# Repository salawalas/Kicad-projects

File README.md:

This is a base of my KiCad projects.

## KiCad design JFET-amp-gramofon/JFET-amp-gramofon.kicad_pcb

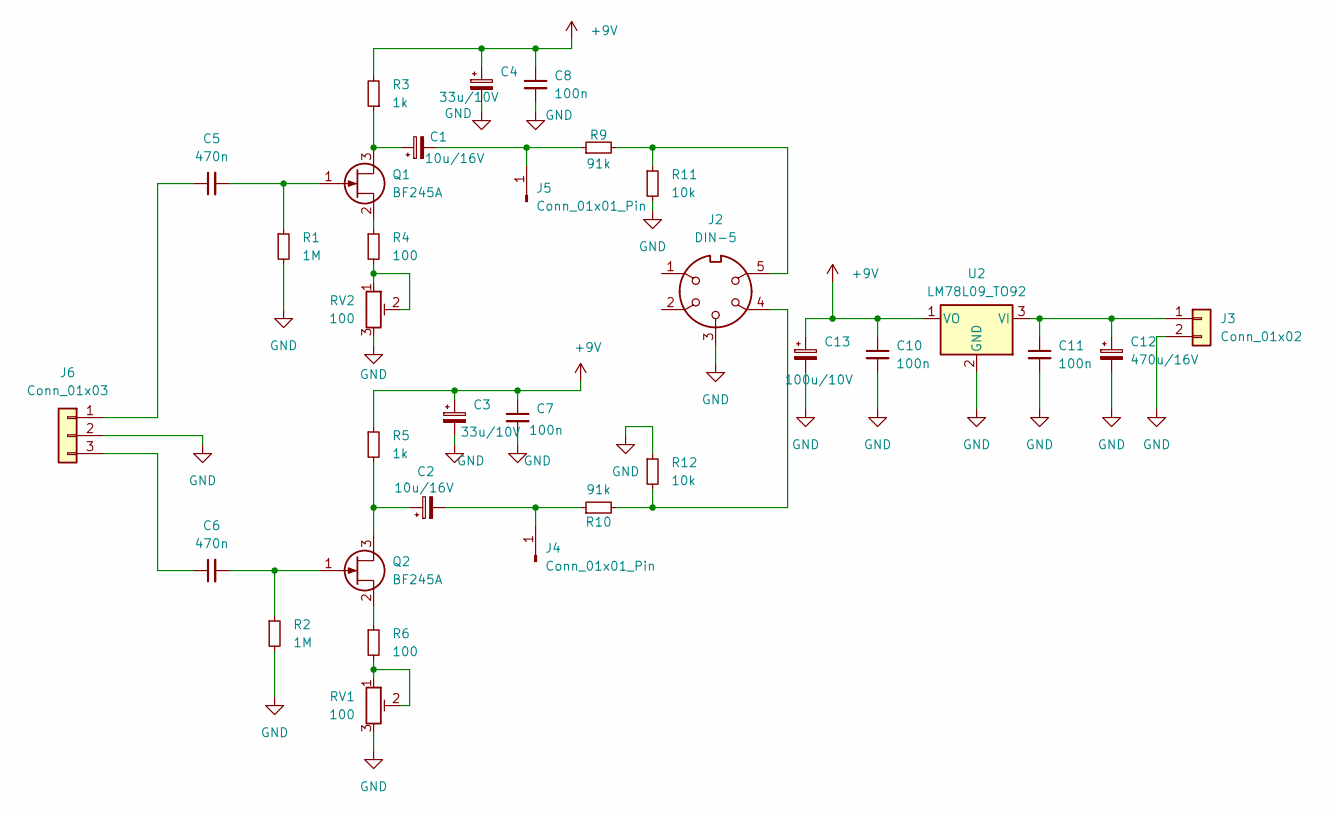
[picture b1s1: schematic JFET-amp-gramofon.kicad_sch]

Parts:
C1, C2: 10u/16V; CP_Radial_D6.3mm_P2.50mm
C3, C4: 33u/10V; CP_Radial_Tantal_D5.5mm_P5.00mm
C5, C6: 470n; C_0805_2012Metric
C7, C8, C10, C11: 100n; C_1206_3216Metric_Pad1.33x1.80mm_HandSolder
C12: 470u/16V; CP_Radial_D10.0mm_P5.00mm
C13: 100u/10V; CP_Radial_D8.0mm_P2.50mm
J2: DIN-5; DIN_5
J3: Conn_01x02; Molex_KK-254_AE-6410-02A_1x02_P2.54mm_Vertical
J4, J5: Conn_01x01_Pin; Pin_D1.3mm_L11.0mm
J6: Conn_01x03; JST_PH_B3B-PH-K_1x03_P2.00mm_Vertical
Q1, Q2: BF245A; TO-92_HandSolder
R1, R2: 1M; R_1206_3216Metric_Pad1.30x1.75mm_HandSolder
R3, R5: 1k; R_1206_3216Metric_Pad1.30x1.75mm_HandSolder
R4, R6: 100; R_1206_3216Metric_Pad1.30x1.75mm_HandSolder
R9, R10: 91k; R_1206_3216Metric_Pad1.30x1.75mm_HandSolder
R11, R12: 10k; R_1206_3216Metric_Pad1.30x1.75mm_HandSolder
RV1, RV2: 100; Potencjometr-smd-mały
U2: LM78L09_TO92; TO-92L_HandSolder

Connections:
+9V: C3.1, C4.1, C7.1, C8.1, C10.1, C13.1, R3.2, R5.1, U2.1 (VO)
GND: C3.2, C4.2, C7.2, C8.2, C10.2, C11.2, C12.2, C13.2, J2.3, J3.2, J6.2, R1.2, R2.2, R11.2, R12.1, RV1.3, RV2.3, U2.2 (GND)
unnamed: J2.4, R10.2, R12.2
unnamed: J2.5, R9.2, R11.1
unnamed: C11.1, C12.1, J3.1, U2.3 (VI)
unnamed: C2.2, J4.1, R10.1
unnamed: C1.2, J5.1, R9.1
unnamed: C5.1, J6.1
unnamed: C6.1, J6.3
unnamed: C1.1, Q1.3 (D), R3.1
unnamed: C5.2, Q1.1 (G), R1.1
unnamed: Q1.2 (S), R4.1
unnamed: C2.1, Q2.3 (D), R5.2
unnamed: C6.2, Q2.1 (G), R2.1
unnamed: Q2.2 (S), R6.1
unnamed: R4.2, RV2.1, RV2.2
unnamed: R6.2, RV1.1, RV1.2

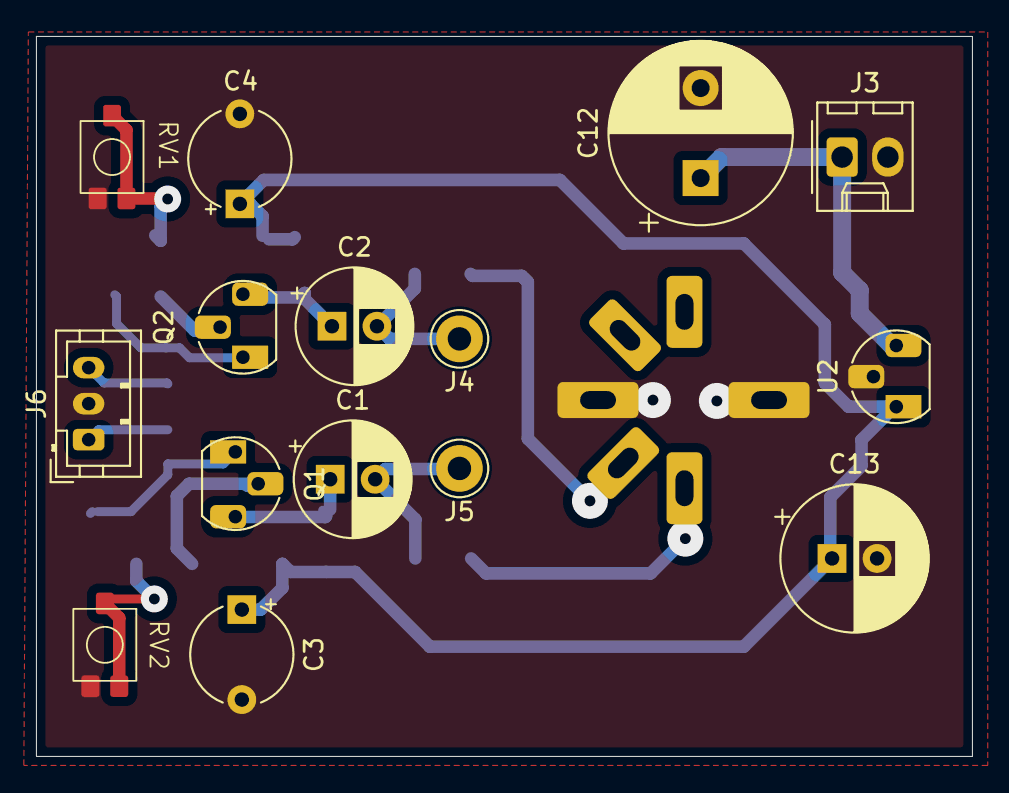
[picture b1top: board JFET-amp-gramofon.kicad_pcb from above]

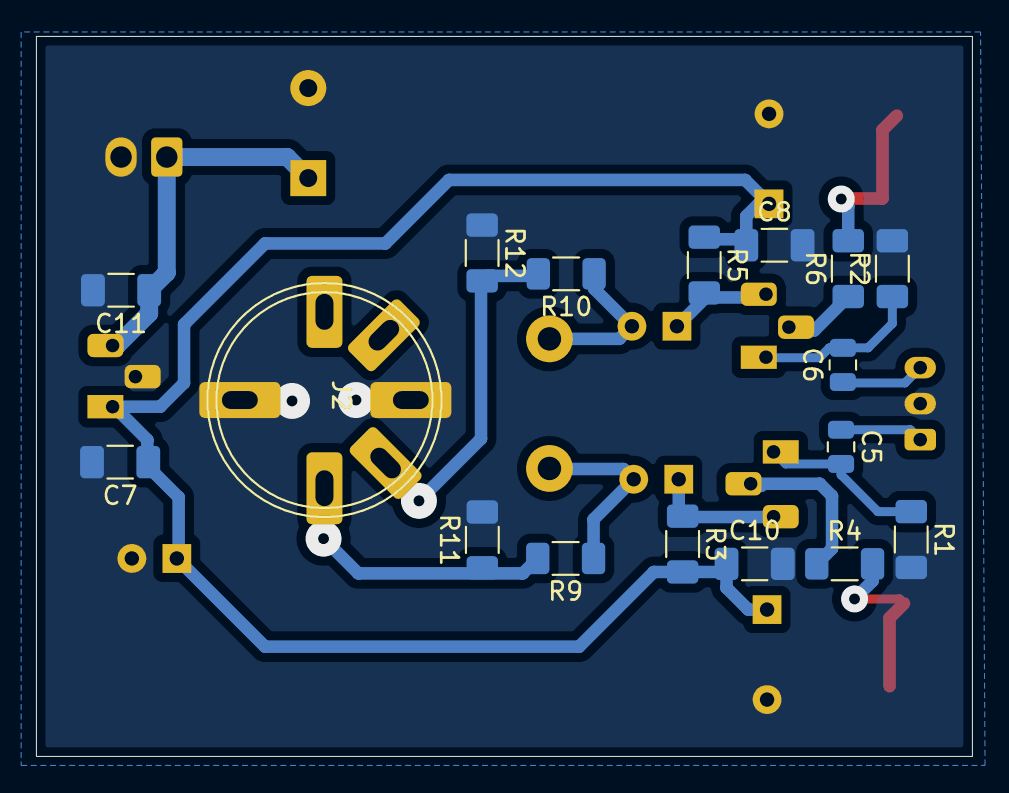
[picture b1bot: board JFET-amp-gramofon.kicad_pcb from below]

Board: 2 copper layers, 52.0 x 40.0 mm, 32 parts (17 on the bottom side), 17 nets.

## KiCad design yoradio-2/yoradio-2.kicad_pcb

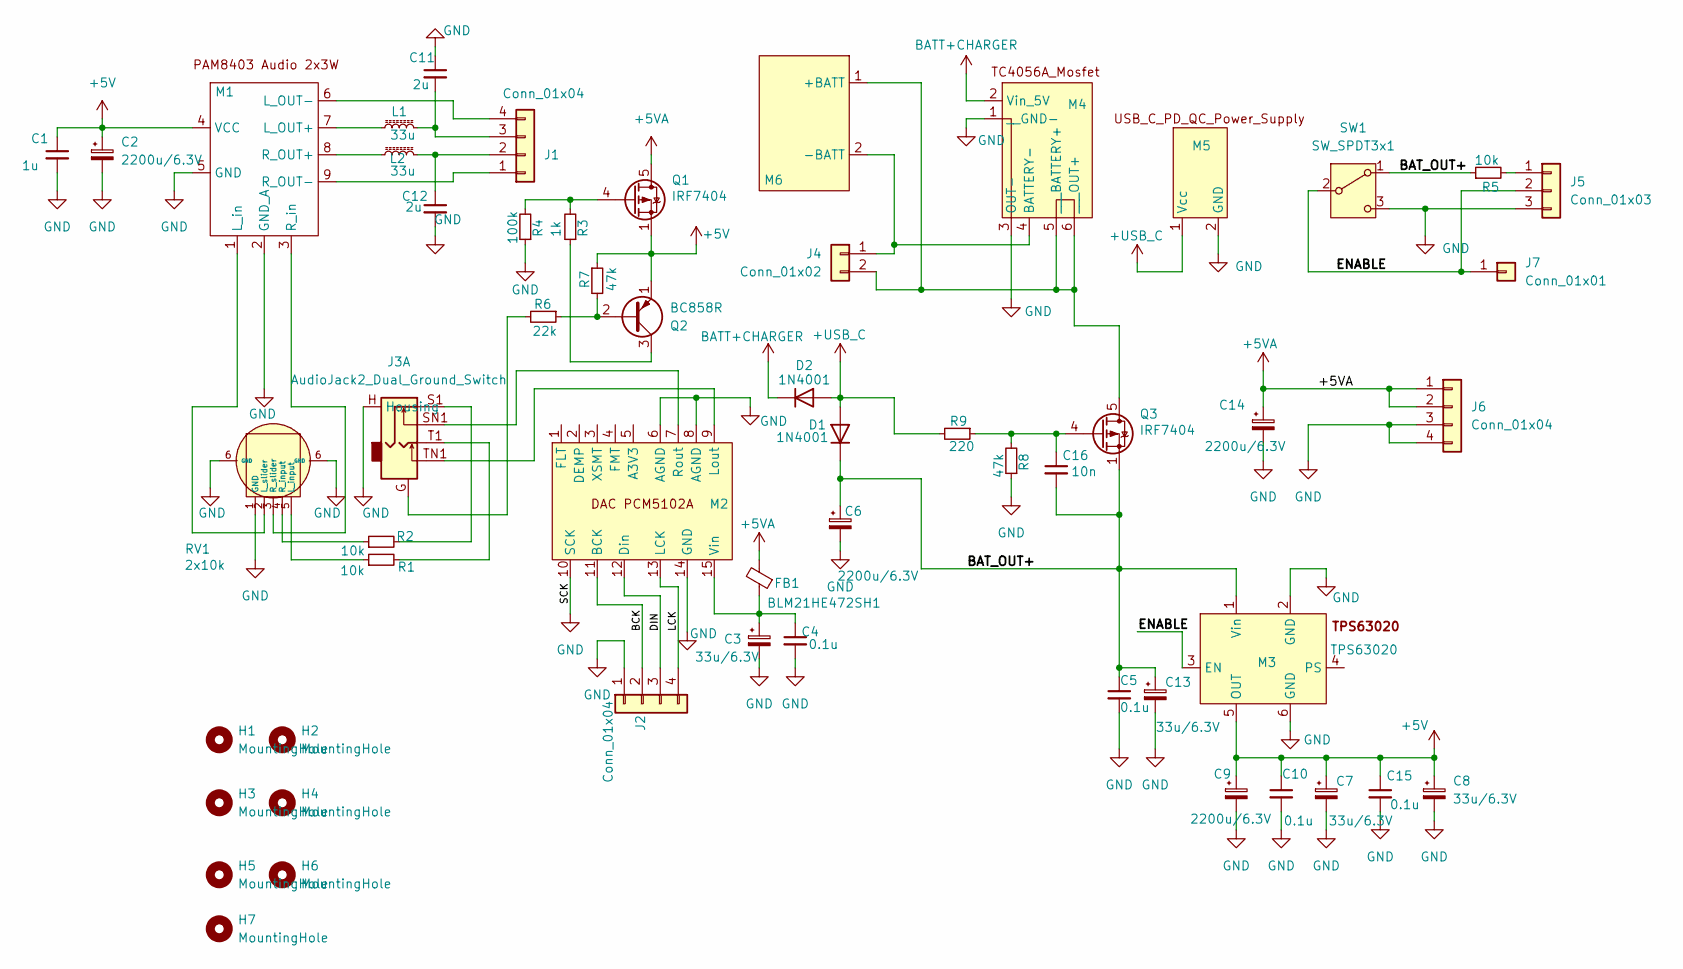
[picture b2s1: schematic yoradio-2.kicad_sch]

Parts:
C1: 1u; C_1206_3216Metric_Pad1.33x1.80mm_HandSolder
C2, C6, C9, C14: 2200u/6.3V; 2200u_6.3V
C3, C7, C8, C13: 33u/6.3V; CP_Radial_Tantal_D5.0mm_P2.50mm
C4, C5, C10, C15: 0.1u; C_1206_3216Metric_Pad1.33x1.80mm_HandSolder
C11, C12: 2u; C_1206_3216Metric_Pad1.33x1.80mm_HandSolder
C16: 10n; C_1206_3216Metric_Pad1.33x1.80mm_HandSolder
D1, D2: 1N4001; D_DO-41_SOD81_P10.16mm_Horizontal
FB1: BLM21HE472SH1; L_0805_2012Metric
H1, H2, H3, H4, H5, H6, H7: MountingHole; MountingHole_2.5mm
J1: Conn_01x04; JST_XH_B4B-XH-A_1x04_P2.50mm_Vertical
J2: Conn_01x04; JST_PH_B4B-PH-K_1x04_P2.00mm_Vertical
J3: AudioJack2_Dual_Ground_Switch; Jack_3.5mm_PJ31060-I_Horizontal
J4: Conn_01x02; Molex_KK-254_AE-6410-02A_1x02_P2.54mm_Vertical
J5: Conn_01x03; JST_PH_B3B-PH-K_1x03_P2.00mm_Vertical
J6: Conn_01x04; Molex_KK-254_AE-6410-04A_1x04_P2.54mm_Vertical
J7: Conn_01x01; SolderWire-0.5sqmm_1x01_D0.9mm_OD2.1mm
L1, L2: 33u; L_Radial_D7.0mm_P3.00mm
M1: PAM8403_Audio_2x3W_
M2: DAC_PCM5102DAC_PCM5102
M3: TPS63020; TPS63020_module
M4: TC4056A_Mosfet
M5: USB_C_PD_QC_Power_SupplyUSB_C_PS
M6: Wskaznik_LED_1S_Lipo
Q1, Q3: IRF7404; SOIC-8_3.9x4.9mm_P1.27mm
Q2: BC858R; SOT-23
R1, R2, R5: 10k; R_0805_2012Metric_Pad1.20x1.40mm_HandSolder
R3: 1k; R_1206_3216Metric
R4: 100k; R_1206_3216Metric
R6: 22k; R_1206_3216Metric
R7: 47k; R_0805_2012Metric
R8: 47k; R_1206_3216Metric
R9: 220; R_1206_3216Metric
RV1: 2x10k; Potencjometr_podwójny_thumbwheel.mp3
SW1: SW_SPDT3x1

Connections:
+5V: C1.1, C2.1, C7.1, C8.1, C9.1, C10.1, C15.1, M1.4 (VCC), M3.5 (OUT), Q1.1 (S), Q1.2 (S), Q1.3 (S), Q2.1 (E), R7.1
+5VA: C14.1, FB1.2, J6.1, J6.2, Q1.5 (D), Q1.6 (D), Q1.7 (D), Q1.8 (D)
+USB_C: D1.2 (A), D2.2 (A), M5.1 (Vcc), R9.2
/BAT_OUT+: C5.1, C6.1, C13.1, C16.2, D1.1 (K), M3.1 (Vin), Q3.1 (S), Q3.2 (S), Q3.3 (S), R5.1, SW1.1 (A)
/BCK: J2.2, M2.11 (BCK)
/DIN: J2.3, M2.12 (Din)
/ENABLE: J5.2, J7.1, M3.3 (EN), SW1.2 (B)
/LCK: J2.4, M2.13 (LCK)
BATT+CHARGER: D2.1 (K), M4.2 (Vin_5V)
GND: C1.2, C2.2, C3.2, C4.2, C5.2, C6.2, C7.2, C8.2, C9.2, C10.2, C11.1, C12.2, C13.2, C14.2, C15.2, J2.1, J3.H (Housing), J5.3, J6.3, J6.4, M1.2 (GND_A), M1.5 (GND), M2.6 (AGND), M2.8 (AGND), M2.10 (SCK), M2.14 (GND), M3.2 (GND), M3.6 (GND), M4.1 (__GND-), M4.3 (OUT-), M5.2 (GND), R4.1, R8.1, RV1.1 (GND), RV1.6 (GND), SW1.3 (C)
unnamed: J1.1, M1.9 (R_OUT-)
unnamed: C12.1, J1.2, L2.2
unnamed: C11.2, J1.3, L1.2
unnamed: J1.4, M1.6 (L_OUT-)
unnamed: J3.G, R6.2
unnamed: J3.S1, R2.2
unnamed: J3.T1, R1.2
unnamed: J4.1, M4.4 (BATTERY-), M6.2 (-BATT)
unnamed: J4.2, M4.5 (___BATTERY+), M4.6 (___OUT+), M6.1 (+BATT), Q3.5 (D), Q3.6 (D), Q3.7 (D), Q3.8 (D)
unnamed: J5.1, R5.2
unnamed: L1.1, M1.7 (L_OUT+)
unnamed: M1.1 (L_in), RV1.2 (L_slider)
unnamed: L2.1, M1.8 (R_OUT+)
unnamed: M1.3 (R_in), RV1.3 (R_slider)
unnamed: J3.TN1, M2.9 (Lout)
unnamed: J3.SN1, M2.7 (Rout)
unnamed: C3.1, C4.1, FB1.1, M2.15 (Vin)
unnamed: Q1.4 (G), R3.2, R4.2
unnamed: Q2.2 (B), R6.1, R7.2
unnamed: Q2.3 (C), R3.1
unnamed: C16.1, Q3.4 (G), R8.2, R9.1
unnamed: R1.1, RV1.5 (L_input)
unnamed: R2.1, RV1.4 (R_input)

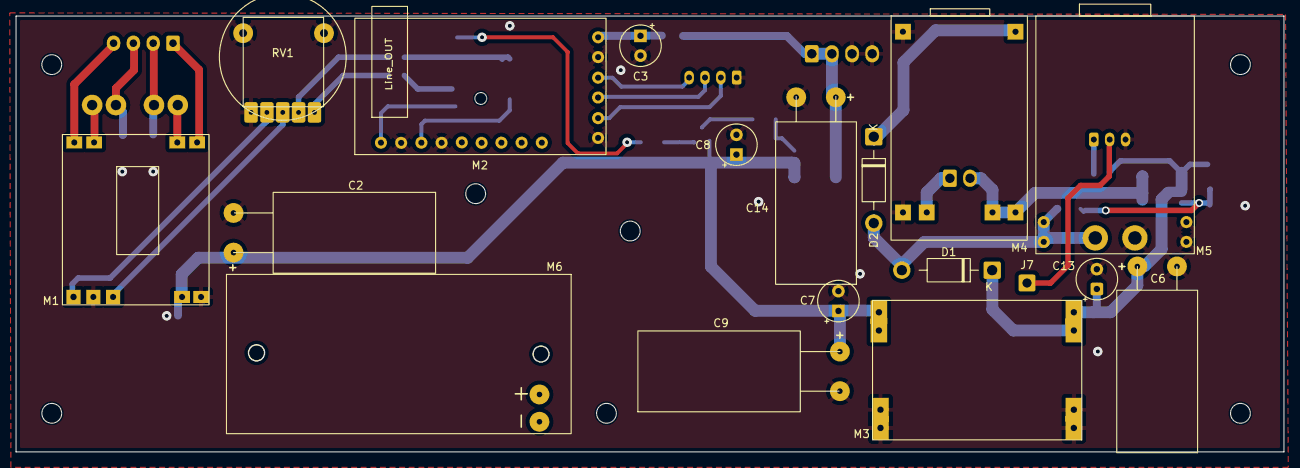
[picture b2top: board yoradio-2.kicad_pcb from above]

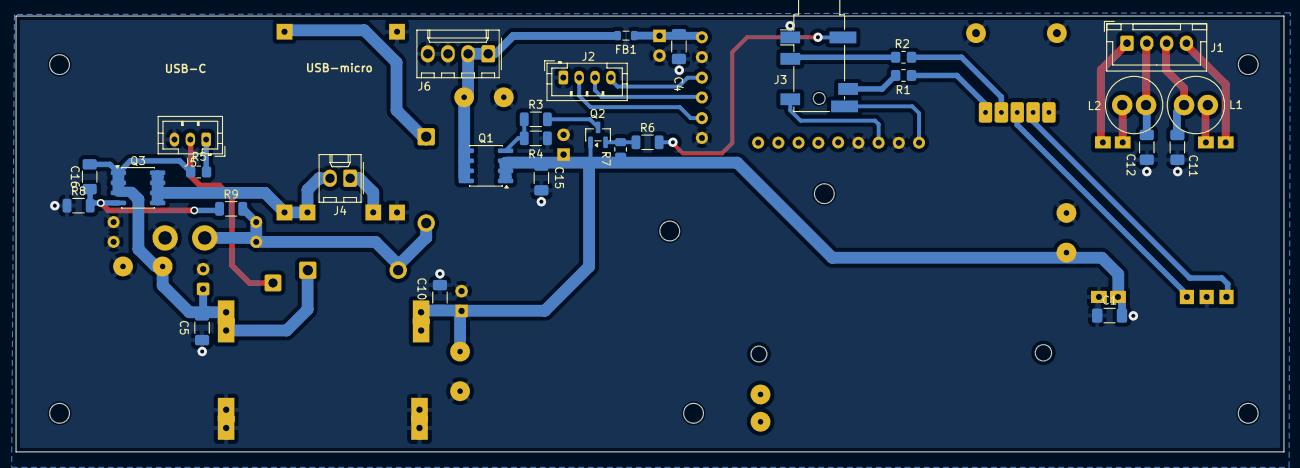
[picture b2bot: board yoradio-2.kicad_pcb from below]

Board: 2 copper layers, 159.9 x 54.9 mm, 54 parts (29 on the bottom side), 33 nets.

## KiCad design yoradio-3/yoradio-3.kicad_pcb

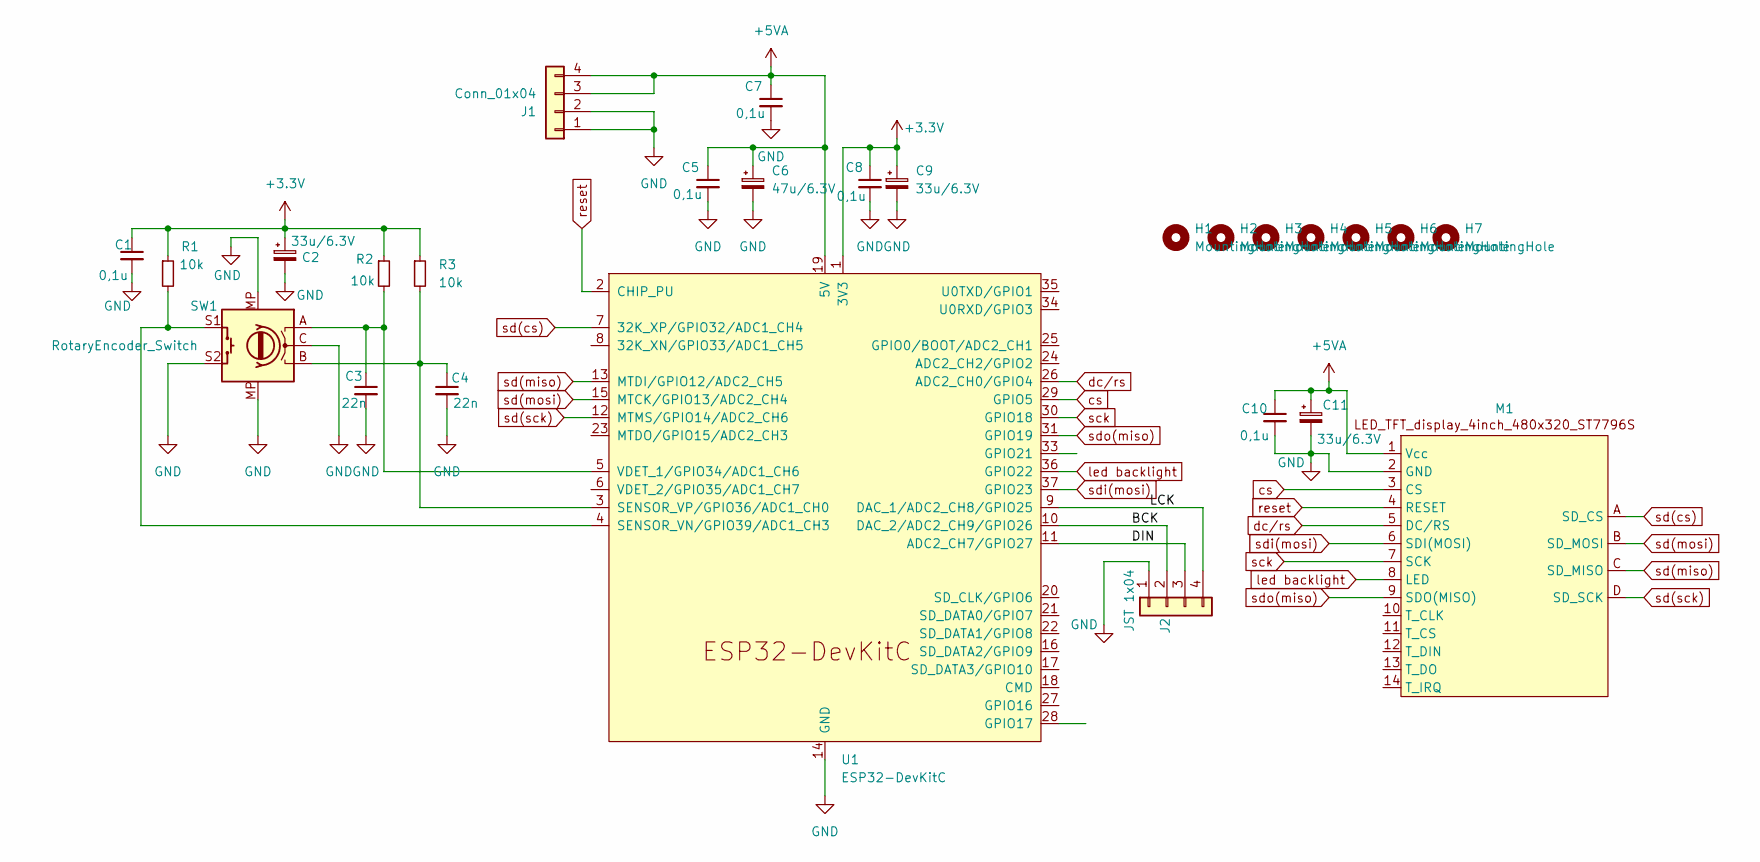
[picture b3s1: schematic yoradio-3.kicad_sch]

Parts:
C1, C5, C7, C8, C10: 0,1u; C_1206_3216Metric_Pad1.33x1.80mm_HandSolder
C2, C9, C11: 33u/6.3V; CP_Radial_Tantal_D7.0mm_P5.00mm
C3, C4: 22n; C_1206_3216Metric_Pad1.33x1.80mm_HandSolder
C6: 47u/6.3V; CP_Radial_Tantal_D7.0mm_P5.00mm
H1, H2, H3, H4, H5, H6, H7: MountingHole; MountingHole_2.5mm
J1: Conn_01x04; Molex_KK-254_AE-6410-04A_1x04_P2.54mm_Vertical
J2: JST 1x04; JST_PH_B4B-PH-K_1x04_P2.00mm_Vertical
M1: TFT_displayLED_TFT_display_4inch_480x320_ST7796S
R1, R2, R3: 10k; R_1206_3216Metric_Pad1.30x1.75mm_HandSolder
SW1: RotaryEncoder_Switch; RotaryEncoder_Alps_EC11E-Switch_Vertical_H20mm
U1: ESP32-DevKitC; ESP32-DevKitC_ver2

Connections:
+3.3V: C1.1, C2.1, C8.1, C9.1, R1.1, R2.1, R3.1, U1.1 (3V3)
+5VA: C5.1, C6.1, C7.1, C10.1, C11.1, J1.3, J1.4, M1.1 (Vcc), U1.19 (5V)
/BCK: J2.2, U1.10 (DAC_2/ADC2_CH9/GPIO26)
/DIN: J2.3, U1.11 (ADC2_CH7/GPIO27)
/LCK: J2.4, U1.9 (DAC_1/ADC2_CH8/GPIO25)
GND: C1.2, C2.2, C3.2, C4.2, C5.2, C6.2, C7.2, C8.2, C9.2, C10.2, C11.2, J1.1, J1.2, J2.1, M1.2 (GND), SW1.C, SW1.MP, SW1.S2, U1.14 (GND), U1.32 (GND), U1.38 (GND)
unnamed: R1.2, SW1.S1, U1.4 (SENSOR_VN/GPIO39/ADC1_CH3)
unnamed: C4.1, R3.2, SW1.B, U1.3 (SENSOR_VP/GPIO36/ADC1_CH0)
unnamed: C3.1, R2.2, SW1.A, U1.5 (VDET_1/GPIO34/ADC1_CH6)
cs: M1.3 (CS), U1.29 (GPIO5)
dc/rs: M1.5 (DC/RS), U1.26 (ADC2_CH0/GPIO4)
led backlight: M1.8 (LED), U1.36 (GPIO22)
reset: M1.4 (RESET), U1.2 (CHIP_PU)
sck: M1.7 (SCK), U1.30 (GPIO18)
sd(cs): M1.A (SD_CS), U1.7 (32K_XP/GPIO32/ADC1_CH4)
sd(miso): M1.C (SD_MISO), U1.13 (MTDI/GPIO12/ADC2_CH5)
sd(mosi): M1.B (SD_MOSI), U1.15 (MTCK/GPIO13/ADC2_CH4)
sd(sck): M1.D (SD_SCK), U1.12 (MTMS/GPIO14/ADC2_CH6)
sdi(mosi): M1.6 (SDI(MOSI)), U1.37 (GPIO23)
sdo(miso): M1.9 (SDO(MISO)), U1.31 (GPIO19)

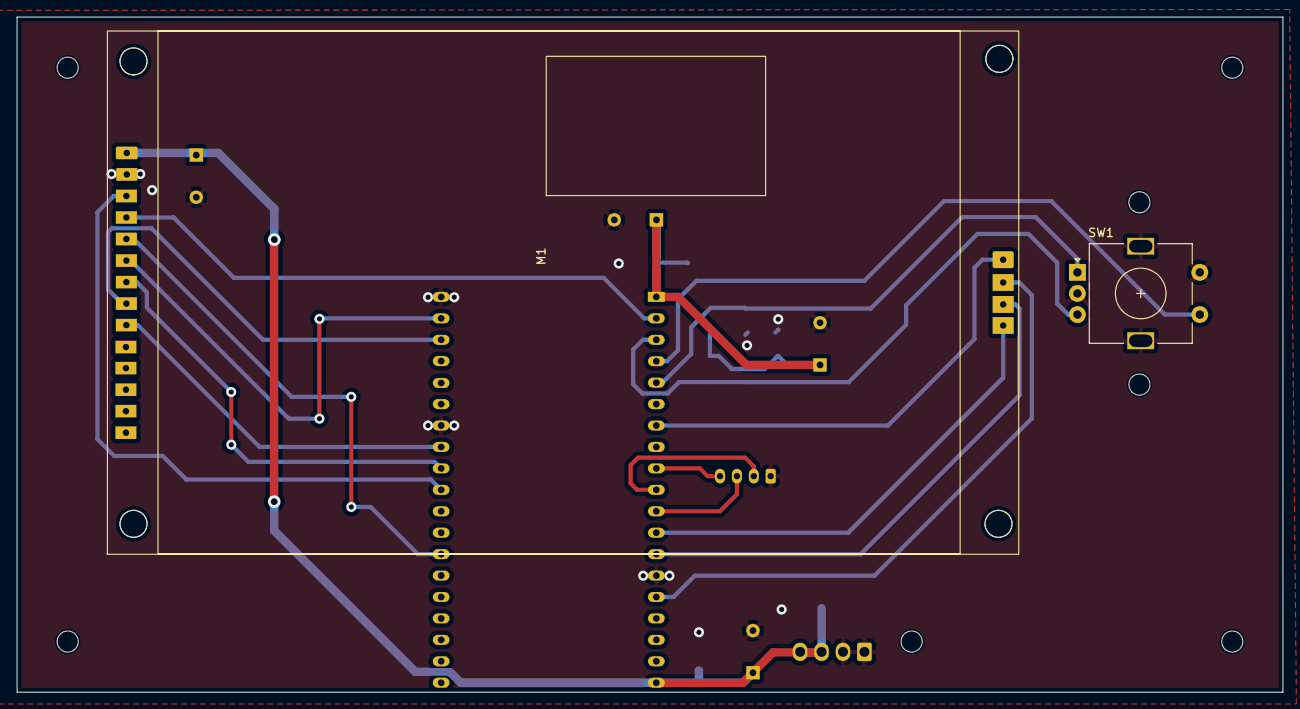
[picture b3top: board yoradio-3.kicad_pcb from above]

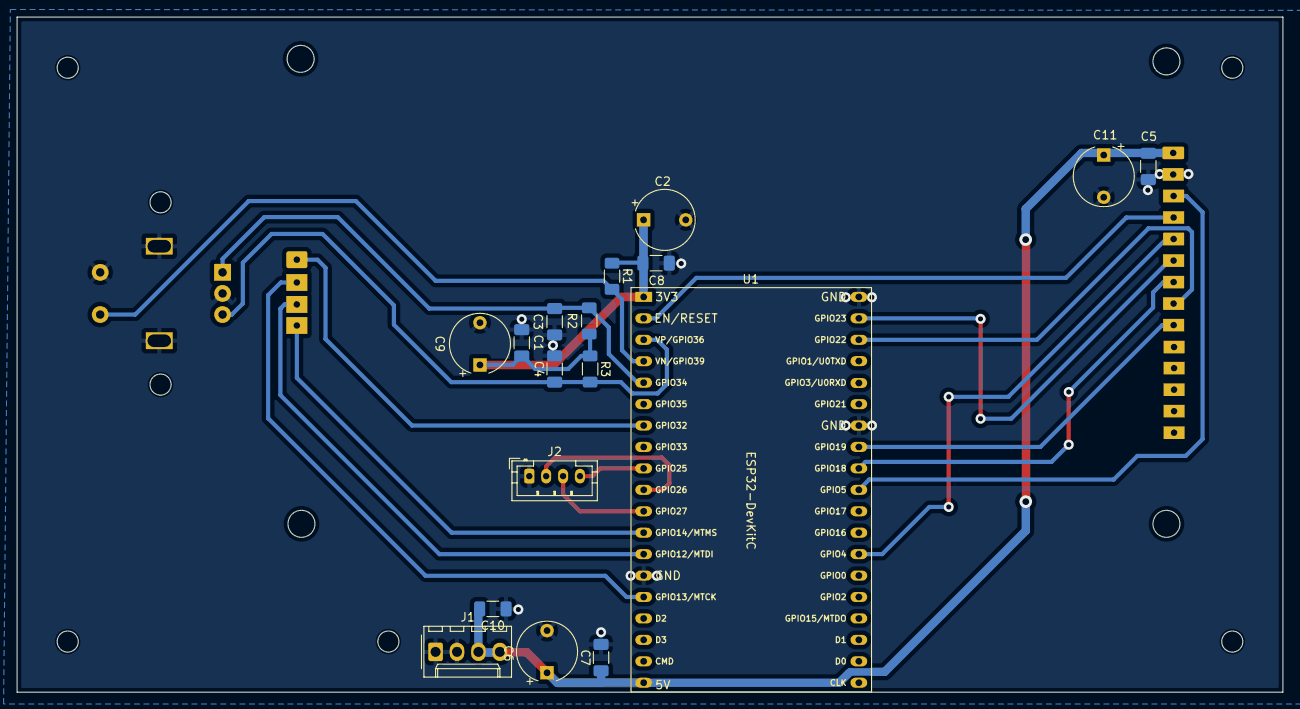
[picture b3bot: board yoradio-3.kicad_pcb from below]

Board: 2 copper layers, 149.9 x 79.9 mm, 26 parts (17 on the bottom side), 20 nets.

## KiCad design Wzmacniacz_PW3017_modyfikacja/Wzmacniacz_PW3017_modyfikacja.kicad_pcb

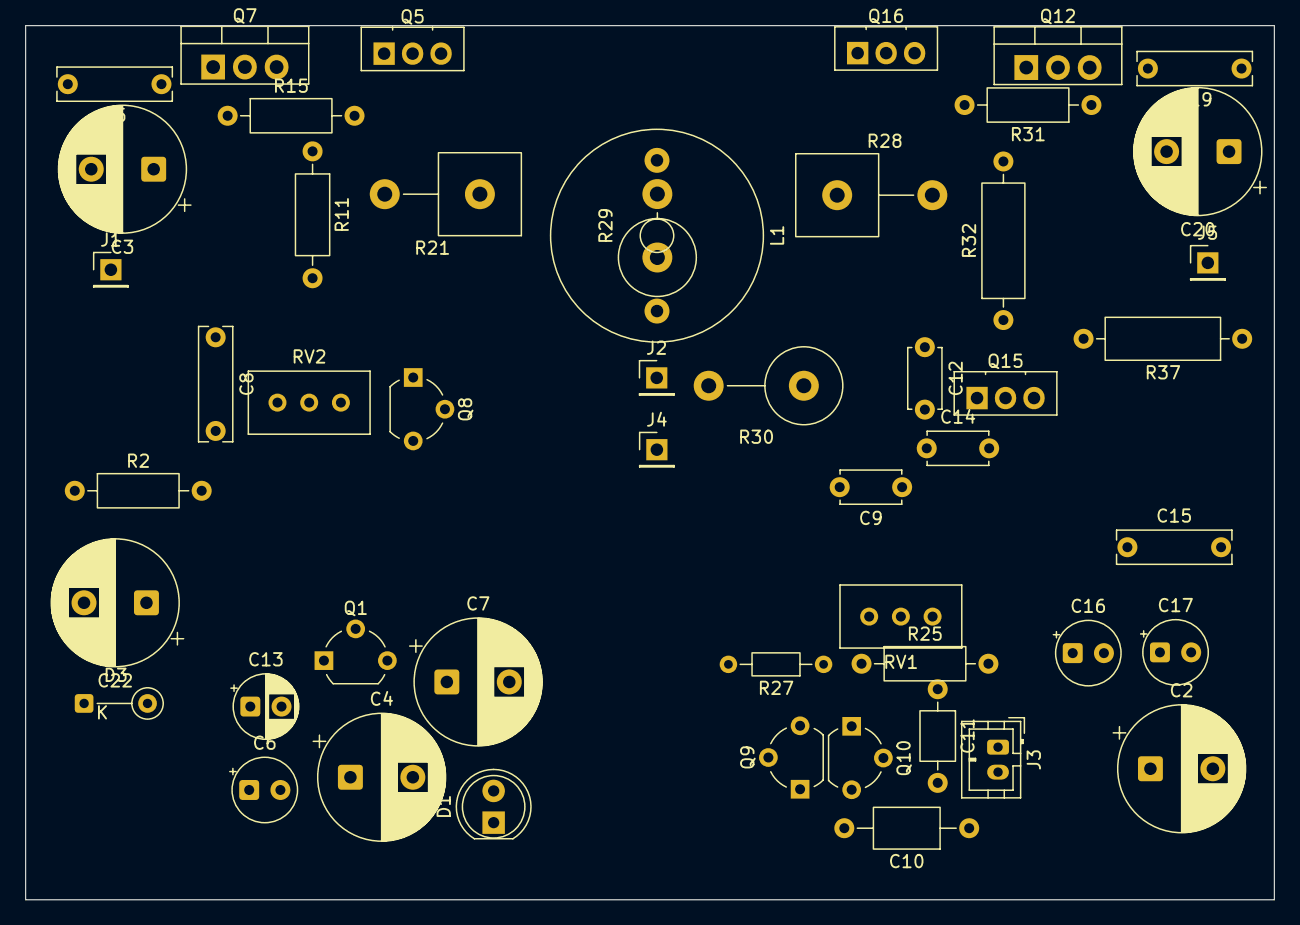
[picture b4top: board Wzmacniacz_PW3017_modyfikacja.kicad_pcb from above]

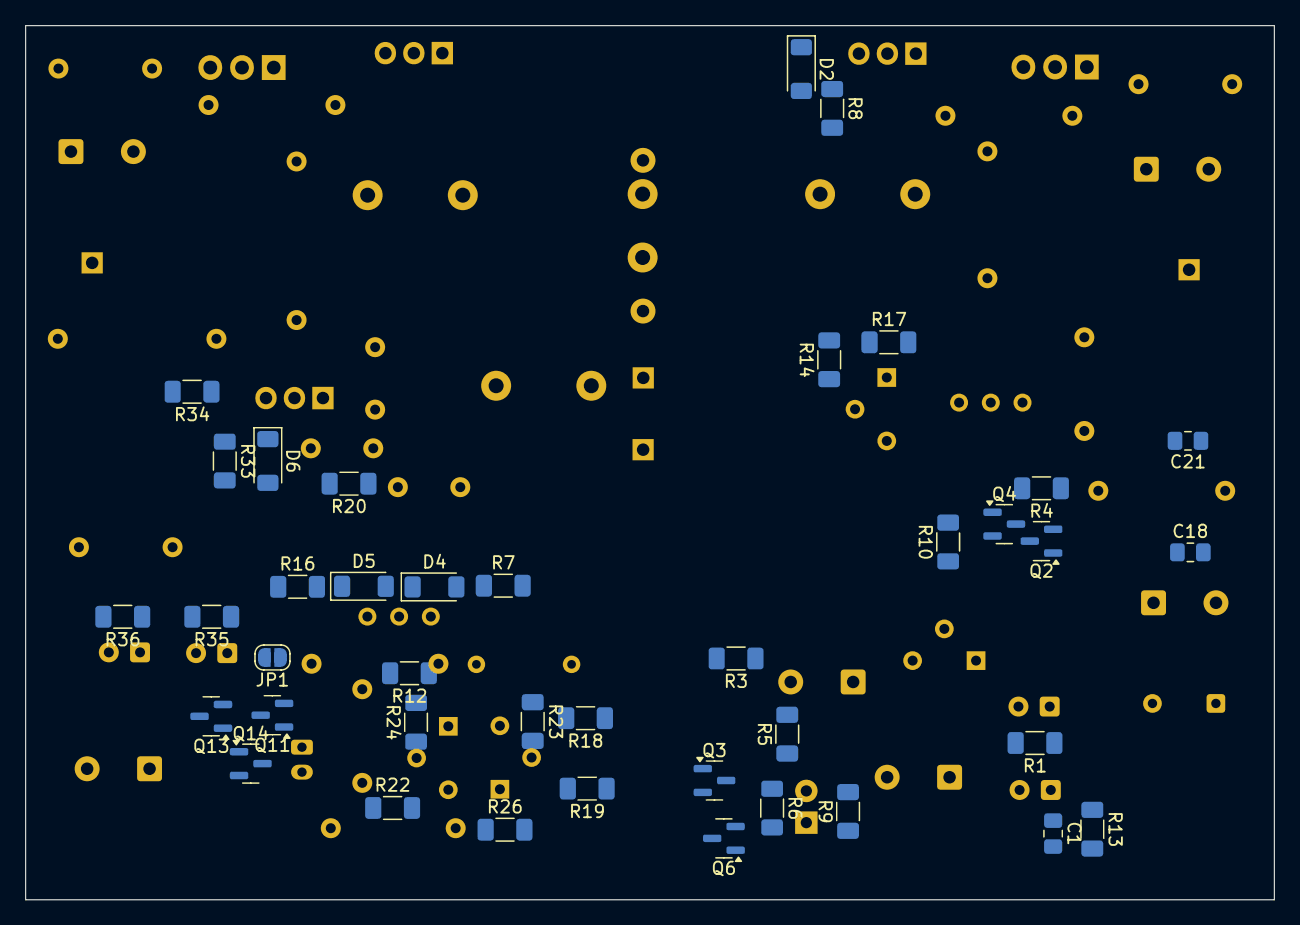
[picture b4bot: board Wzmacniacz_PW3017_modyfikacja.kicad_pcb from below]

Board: 2 copper layers, 100.0 x 70.0 mm, 90 parts (40 on the bottom side), 49 nets, no tracks yet.

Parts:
C1, C18, C21: 100n; C_0805_2012Metric_Pad1.18x1.45mm_HandSolder
C2: 470u/16V; CP_Radial_D10.0mm_P5.00mm
C3, C20, C22: 470u/35V; CP_Radial_D10.0mm_P5.00mm
C4: 220u/35V; CP_Radial_D10.0mm_P5.00mm
C5, C19: 100n; C_Rect_L9.0mm_W2.5mm_P7.50mm_MKT
C6, C16, C17: 33u/25V; CP_Radial_Tantal_D5.0mm_P2.50mm
C7: 220u/16V; CP_Radial_D10.0mm_P5.00mm
C8: 0.68U/35v; C_Rect_L9.0mm_W2.5mm_P7.50mm_MKT
C9: 2p2; C_Disc_D4.7mm_W2.5mm_P5.00mm
C10: 2u2; C_Axial_L5.1mm_D3.1mm_P10.00mm_Horizontal
C11: 2n7; C_Axial_L3.8mm_D2.6mm_P7.50mm_Horizontal
C12: 8p2; C_Disc_D4.7mm_W2.5mm_P5.00mm
C13: 100u/25V; CP_Radial_D5.0mm_P2.50mm
C14: 24p; C_Disc_D4.7mm_W2.5mm_P5.00mm
C15: 0.1u; C_Rect_L9.0mm_W2.5mm_P7.50mm_MKT
D1: LED_Small; LED_D5.0mm
D2, D4, D5, D6: LL4148; D_MiniMELF
D3: 16V; D_DO-34_SOD68_P5.08mm_Vertical_KathodeUp
J1: +VCC; PinHeader_1x01_P2.54mm_Vertical
J2: OUT; PinHeader_1x01_P2.54mm_Vertical
J3: INPUT; JST_PH_B2B-PH-K_1x02_P2.00mm_Vertical
J4: GND; PinHeader_1x01_P2.54mm_Vertical
J5: -VEE; PinHeader_1x01_P2.54mm_Vertical
JP1: Jumper_2_Open; SolderJumper-2_P1.3mm_Open_RoundedPad1.0x1.5mm
L1: 4u7; L_Radial_D16.8mm_P12.07mm_Vishay_IHB-1
Q1, Q8: BC237; TO-92_Wide
Q2, Q3, Q4, Q6: BC856R; BC556R
Q5: BD139; TO-126-3_Vertical
Q7: BD911; TO-220-3_Vertical
Q9, Q10: BC560C; TO-92_Wide
Q11, Q13, Q14: BC846; SOT-23
Q12: BD912; TO-220-3_Vertical
Q15: BF459; TO-126-3_Vertical
Q16: BD140; TO-126-3_Vertical
R1: 10; R_1206_3216Metric_Pad1.30x1.75mm_HandSolder
R2: 10; R_Axial_DIN0207_L6.3mm_D2.5mm_P10.16mm_Horizontal
R3: 2k; R_1206_3216Metric_Pad1.30x1.75mm_HandSolder
R4: 91; R_1206_3216Metric_Pad1.30x1.75mm_HandSolder
R5: 360; R_1206_3216Metric_Pad1.30x1.75mm_HandSolder
R6: 100k; R_1206_3216Metric_Pad1.30x1.75mm_HandSolder
R7, R10, R16: 47K; R_1206_3216Metric_Pad1.30x1.75mm_HandSolder
R8, R20, R23, R24, R33: 47; R_1206_3216Metric_Pad1.30x1.75mm_HandSolder
R9: 560; R_1206_3216Metric_Pad1.30x1.75mm_HandSolder
R11, R15, R31: 100; R_Axial_DIN0207_L6.3mm_D2.5mm_P10.16mm_Horizontal
R12: 100K; R_1206_3216Metric_Pad1.30x1.75mm_HandSolder
R13: 3k3; R_1206_3216Metric_Pad1.30x1.75mm_HandSolder
R14: 1k5; R_1206_3216Metric_Pad1.30x1.75mm_HandSolder
R17: 470; R_1206_3216Metric_Pad1.30x1.75mm_HandSolder
R18, R19: 68; R_1206_3216Metric_Pad1.30x1.75mm_HandSolder
R21, R28: 0.47; R_Axial_Power_L20.0mm_W6.4mm_P7.62mm_Vertical
R22: 820; R_1206_3216Metric_Pad1.30x1.75mm_HandSolder
R25: 56k; R_Axial_DIN0207_L6.3mm_D2.5mm_P10.16mm_Horizontal
R26: 56k; R_1206_3216Metric_Pad1.30x1.75mm_HandSolder
R27: 3k9; R_Axial_DIN0204_L3.6mm_D1.6mm_P7.62mm_Horizontal
R29: 10; R_Axial_DIN0617_L17.0mm_D6.0mm_P5.08mm_Vertical
R30: 10; R_Axial_DIN0617_L17.0mm_D6.0mm_P7.62mm_Vertical
R32: 100; R_Axial_DIN0309_L9.0mm_D3.2mm_P12.70mm_Horizontal
R34: 82; R_1206_3216Metric_Pad1.30x1.75mm_HandSolder
R35, R36: 75; R_1206_3216Metric_Pad1.30x1.75mm_HandSolder
R37: 10; R_Axial_DIN0309_L9.0mm_D3.2mm_P12.70mm_Horizontal
RV1: 5K; Potentiometer_Bourns_3296W_Vertical
RV2: 500; Potentiometer_Bourns_3296W_Vertical

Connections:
/+15V: C1.1, C2.1, C6.1, D1.2 (A), R1.1, R5.1, R6.1
/FB_SUM: C9.2, R12.2, R24.2, R25.1, R27.1
/VC+: C4.1, Q1.1 (C), Q2.2 (E), R2.2, R3.1, R4.1
/VCC+: C3.1, C5.1, D2.1 (K), J1.1, Q5.2 (C), Q7.2 (C), R2.1
/VE-: C16.2, C17.2, C18.2, C21.1, C22.2, R34.1, R35.2, R36.2, R37.2
/VEE-: C19.2, C20.2, J5.1, Q12.2 (C), Q16.2 (C), R37.1
GND: C1.2, C2.2, C3.2, C4.2, C5.2, C7.2, C11.2, C13.2, C15.2, C18.1, C19.1, C20.1, C21.2, C22.1, D3.2 (A), D4.1 (K), D5.2 (A), J3.1, J4.1, Q11.3 (C), R13.2, R26.2
unnamed: C9.1, R20.1
unnamed: C10.2, R22.1, R26.1
unnamed: C11.1, R22.2, R23.1
unnamed: C12.1, L1.1, R21.1, R25.2, R28.1, R29.2
unnamed: C13.1, R27.2
unnamed: C15.1, R30.1
unnamed: D1.1 (K), Q3.1 (B), R6.2, R9.1, R10.2
unnamed: D2.2 (A), R8.1
unnamed: C7.1, D3.1 (K), Q1.2 (B), R3.2
unnamed: D4.2 (A), R7.1, RV1.1
unnamed: D5.1 (K), R16.2, RV1.3
unnamed: C12.2, C14.1, D6.2 (A), Q9.1 (C), Q13.3 (C), R33.2
unnamed: C8.2, C14.2, D6.1 (K), Q8.3 (E), Q15.2 (C), R20.2, R32.1, RV2.2, RV2.3
unnamed: J2.1, L1.2, R29.1, R30.2
unnamed: C10.1, J3.2
unnamed: JP1.1 (A), Q11.2 (E), Q13.1 (B), Q14.1 (B)
unnamed: JP1.2 (B), Q10.1 (C), Q11.1 (B), Q14.3 (C)
unnamed: Q1.3 (E), R1.2
unnamed: Q2.1 (B), Q4.2 (E), R4.2
unnamed: Q2.3 (C), Q4.1 (B), R10.1
unnamed: Q3.3 (C), Q6.2 (E)
unnamed: Q3.2 (E), R5.2
unnamed: C8.1, Q4.3 (C), Q8.1 (C), R8.2, R11.2, R14.1
unnamed: Q5.3 (B), R11.1
unnamed: Q5.1 (E), Q7.1 (B), R15.1
unnamed: C6.2, Q6.1 (B), R9.2, R13.1
unnamed: Q6.3 (C), R18.1, R19.1
unnamed: Q7.3 (E), R15.2, R21.2
unnamed: Q8.2 (B), R14.2, R17.1
unnamed: Q9.2 (B), R23.2
unnamed: Q9.3 (E), R18.2
unnamed: Q10.2 (B), R24.1
unnamed: Q10.3 (E), R19.2
unnamed: Q12.1 (B), Q16.1 (E), R31.2
unnamed: Q12.3 (E), R28.2, R31.1
unnamed: C16.1, Q13.2 (E), R35.1
unnamed: C17.1, Q14.2 (E), R36.1
unnamed: Q15.3 (B), R33.1
unnamed: Q15.1 (E), R34.2
unnamed: Q16.3 (B), R32.2
unnamed: R12.1, RV1.2
unnamed: R17.2, RV2.1

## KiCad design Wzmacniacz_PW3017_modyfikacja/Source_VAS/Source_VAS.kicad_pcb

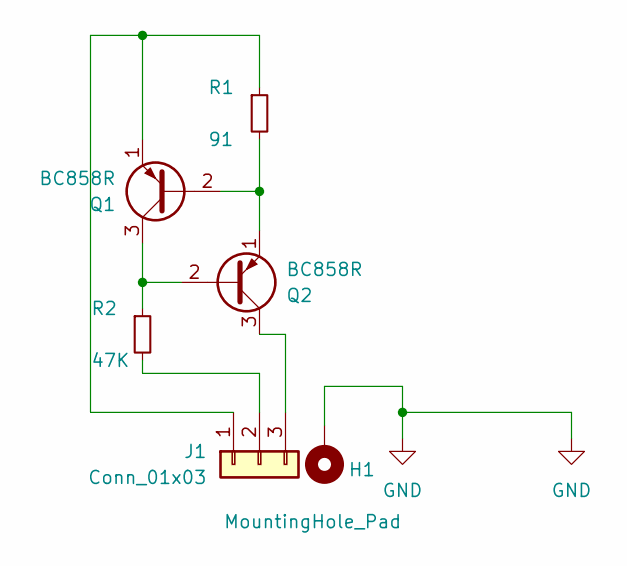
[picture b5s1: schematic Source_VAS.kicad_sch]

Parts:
H1: MountingHole_Pad; SolderWire-0.5sqmm_1x01_D0.9mm_OD2.1mm
J1: Conn_01x03
Q1, Q2: BC858R; SOT-23
R1: 91; R_1206_3216Metric_Pad1.30x1.75mm_HandSolder
R2: 47K; R_1206_3216Metric_Pad1.30x1.75mm_HandSolder

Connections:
GND: H1.1
unnamed: J1.1, Q1.1 (E), R1.1
unnamed: J1.2, R2.2
unnamed: J1.3, Q2.3 (C)
unnamed: Q1.2 (B), Q2.1 (E), R1.2
unnamed: Q1.3 (C), Q2.2 (B), R2.1

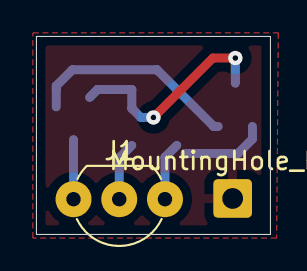
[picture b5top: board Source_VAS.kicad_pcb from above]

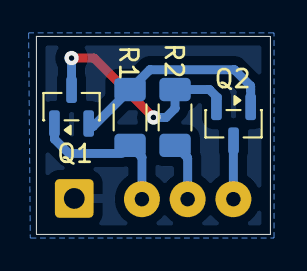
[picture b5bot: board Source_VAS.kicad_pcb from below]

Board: 2 copper layers, 13.0 x 11.0 mm, 6 parts (4 on the bottom side), 5 nets.

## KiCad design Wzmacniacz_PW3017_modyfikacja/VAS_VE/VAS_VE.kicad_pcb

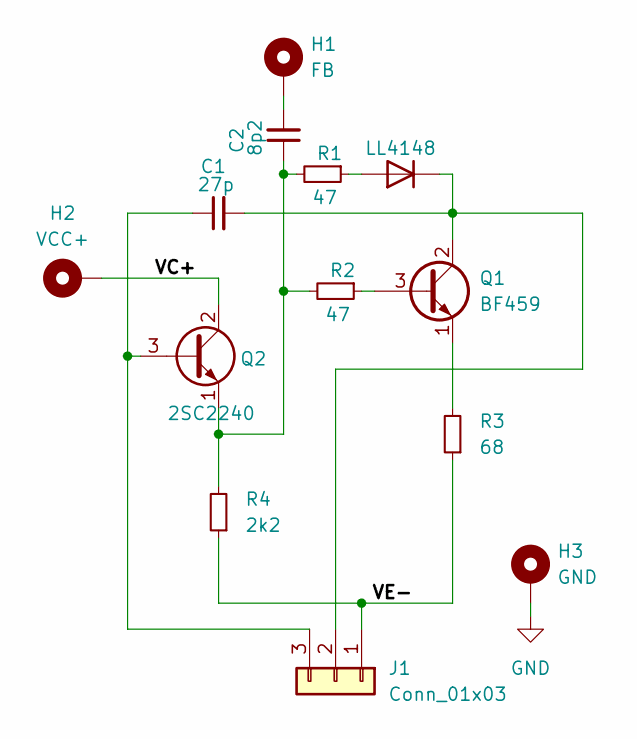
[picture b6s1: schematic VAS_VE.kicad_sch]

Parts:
C1: 27p; C_0805_2012Metric
C2: 8p2; C_0805_2012Metric
D1: LL4148; D_MiniMELF
H1: FB; SolderWire-0.1sqmm_1x01_D0.4mm_OD1mm
H2: VCC+; SolderWire-0.1sqmm_1x01_D0.4mm_OD1mm
H3: GND; SolderWire-0.1sqmm_1x01_D0.4mm_OD1mm
J1: Conn_01x03; PinHeader_1x03_P2.54mm_Horizontal
Q1: BF459; TO-126-3_Vertical
Q2: 2SC2240; TO-92_HandSolder
R1, R2: 47; R_1206_3216Metric_Pad1.30x1.75mm_HandSolder
R3: 68; R_1206_3216Metric_Pad1.30x1.75mm_HandSolder
R4: 2k2; R_1206_3216Metric_Pad1.30x1.75mm_HandSolder

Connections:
/VC+: H2.1, Q2.2 (C)
/VE-: J1.1, R3.1, R4.1
GND: H3.1
unnamed: C2.2, H1.1
unnamed: D1.2 (A), R1.1
unnamed: C1.2, D1.1 (K), J1.2, Q1.2 (C)
unnamed: C1.1, J1.3, Q2.3 (B)
unnamed: Q1.3 (B), R2.1
unnamed: Q1.1 (E), R3.2
unnamed: C2.1, Q2.1 (E), R1.2, R2.2, R4.2

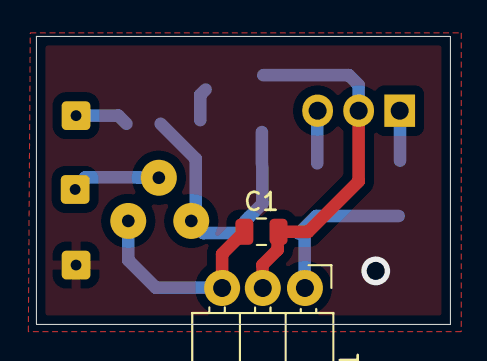
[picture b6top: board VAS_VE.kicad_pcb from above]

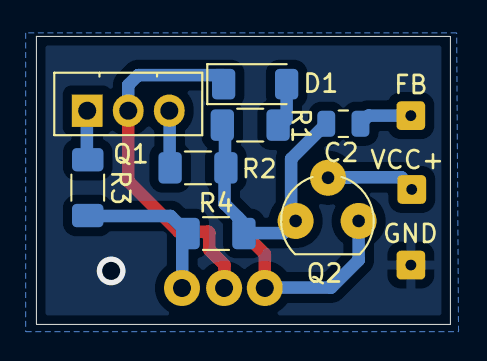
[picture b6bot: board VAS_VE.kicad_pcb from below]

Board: 2 copper layers, 23.0 x 16.0 mm, 13 parts (11 on the bottom side), 9 nets.
